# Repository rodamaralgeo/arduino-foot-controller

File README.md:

# arduino-foot-controller
Foot Controller Midi feito com um Arduino Mega

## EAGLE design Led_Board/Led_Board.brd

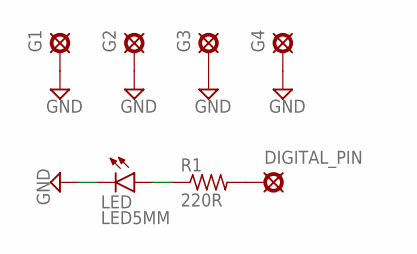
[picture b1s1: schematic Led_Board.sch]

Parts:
DIGITAL_PIN: PADO; ROUND
G1, G2, G3, G4: PADO; ROUND
LED: LED5MM
R1: 220R; R0207/3

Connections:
GND: G1.1, G2.1, G3.1, G4.1, LED.K (C)
unnamed: LED.A, R1.1
unnamed: DIGITAL_PIN.1, R1.2

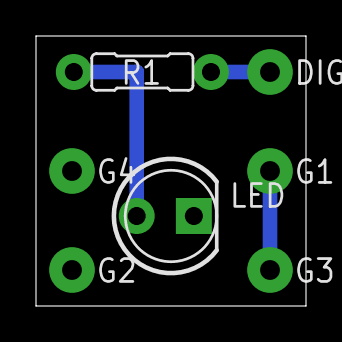
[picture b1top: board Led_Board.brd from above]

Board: 2 copper layers, 15.0 x 15.0 mm, 7 parts (0 on the bottom side), 3 nets.

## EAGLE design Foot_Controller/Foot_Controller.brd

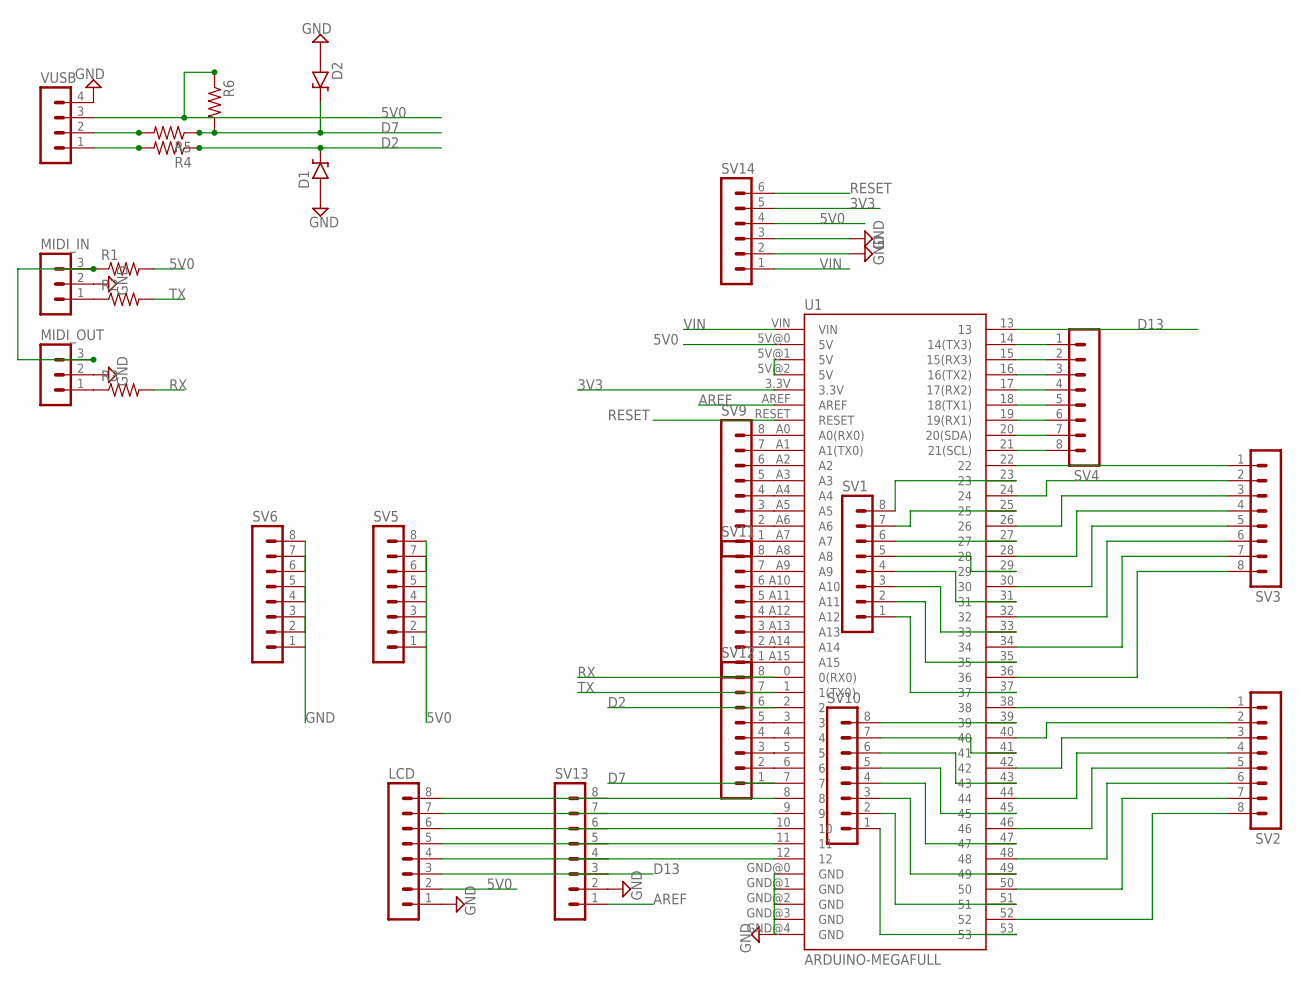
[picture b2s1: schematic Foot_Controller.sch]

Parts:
D1, D2: 1N9ZENER; DO35-3
LCD: MA08-1
MIDI_IN: MA03-1
MIDI_OUT: MA03-1
R1, R2, R3, R4, R5, R6: 6MM.3; R0207/3
SV1, SV2, SV3, SV4, SV5, SV6, SV9, SV10, SV11, SV12, SV13: MA08-1
SV14: MA06-1
U1: ARDUINO-MEGAFULL; ARDUINO_MEGA
VUSB: MA04-1

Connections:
3V3: SV14.5, U1.3.3V
5V0: LCD.2, R1.2, R6.1, SV5.1, SV5.2, SV5.3, SV5.4, SV5.5, SV5.6, SV5.7, SV5.8, SV14.4, U1.5V@0 (5V), VUSB.3
AREF: SV13.1, U1.AREF
D2: D1.C, R4.1, SV12.6, U1.2
D7: D2.C, R5.1, R6.2, SV12.1, U1.7
D13: LCD.3, SV13.3, U1.13
GND: D1.A, D2.A, LCD.1, MIDI_IN.2, MIDI_OUT.2, SV6.1, SV6.2, SV6.3, SV6.4, SV6.5, SV6.6, SV6.7, SV6.8, SV13.2, SV14.2, SV14.3, U1.GND@0 (GND), U1.GND@1 (GND), U1.GND@2 (GND), U1.GND@3 (GND), U1.GND@4 (GND), VUSB.4
unnamed: SV1.8, U1.23
unnamed: SV1.7, U1.25
unnamed: SV1.6, U1.27
unnamed: SV1.5, U1.29
unnamed: SV1.4, U1.31
unnamed: SV1.3, U1.33
unnamed: SV1.2, U1.35
unnamed: SV1.1, U1.37
unnamed: SV2.1, U1.38
unnamed: SV2.2, U1.40
unnamed: SV2.3, U1.42
unnamed: SV2.4, U1.44
unnamed: SV2.5, U1.46
unnamed: SV2.6, U1.48
unnamed: SV2.7, U1.50
unnamed: SV2.8, U1.52
unnamed: SV10.8, U1.39
unnamed: SV10.7, U1.41
unnamed: SV10.6, U1.43
unnamed: SV10.5, U1.45
unnamed: SV10.4, U1.47
unnamed: SV10.3, U1.49
unnamed: SV10.2, U1.51
unnamed: SV10.1, U1.53
unnamed: SV3.2, U1.24
unnamed: SV3.1, U1.22
unnamed: SV3.3, U1.26
unnamed: SV3.4, U1.28
unnamed: SV3.5, U1.30
unnamed: SV3.6, U1.32
unnamed: SV3.7, U1.34
unnamed: SV3.8, U1.36
unnamed: SV4.1, U1.14 (14(TX3))
unnamed: SV4.2, U1.15 (15(RX3))
unnamed: SV4.3, U1.16 (16(TX2))
unnamed: SV4.4, U1.17 (17(RX2))
unnamed: SV4.5, U1.18 (18(TX1))
unnamed: SV4.6, U1.19 (19(RX1))
unnamed: SV4.7, U1.20 (20(SDA))
unnamed: SV4.8, U1.21 (21(SCL))
unnamed: SV9.1, U1.A7
unnamed: SV9.2, U1.A6
unnamed: SV9.3, U1.A5
unnamed: SV9.4, U1.A4
unnamed: SV9.5, U1.A3
unnamed: SV9.6, U1.A2
unnamed: SV9.7, U1.A1 (A1(TX0))
unnamed: SV9.8, U1.A0 (A0(RX0))
unnamed: SV11.1, U1.A15
unnamed: SV11.2, U1.A14
unnamed: SV11.3, U1.A13
unnamed: SV11.4, U1.A12
unnamed: SV11.5, U1.A11
unnamed: SV11.6, U1.A10
unnamed: SV11.7, U1.A9
unnamed: SV11.8, U1.A8
unnamed: U1.5V@1 (5V), U1.5V@2 (5V)
unnamed: SV12.2, U1.6
unnamed: SV12.3, U1.5
unnamed: SV12.4, U1.4
unnamed: SV12.5, U1.3
unnamed: LCD.8, SV13.8, U1.8
unnamed: LCD.7, SV13.7, U1.9
unnamed: LCD.6, SV13.6, U1.10
unnamed: LCD.5, SV13.5, U1.11
unnamed: LCD.4, SV13.4, U1.12
unnamed: MIDI_OUT.1, R3.1
unnamed: MIDI_IN.1, R2.1
unnamed: MIDI_IN.3, MIDI_OUT.3, R1.1
unnamed: R4.2, VUSB.1
unnamed: R5.2, VUSB.2
RESET: SV14.6, U1.RESET
RX: R3.2, SV12.8, U1.0 (0(RX0))
TX: R2.2, SV12.7, U1.1 (1(TX0))
VIN: SV14.1, U1.VIN

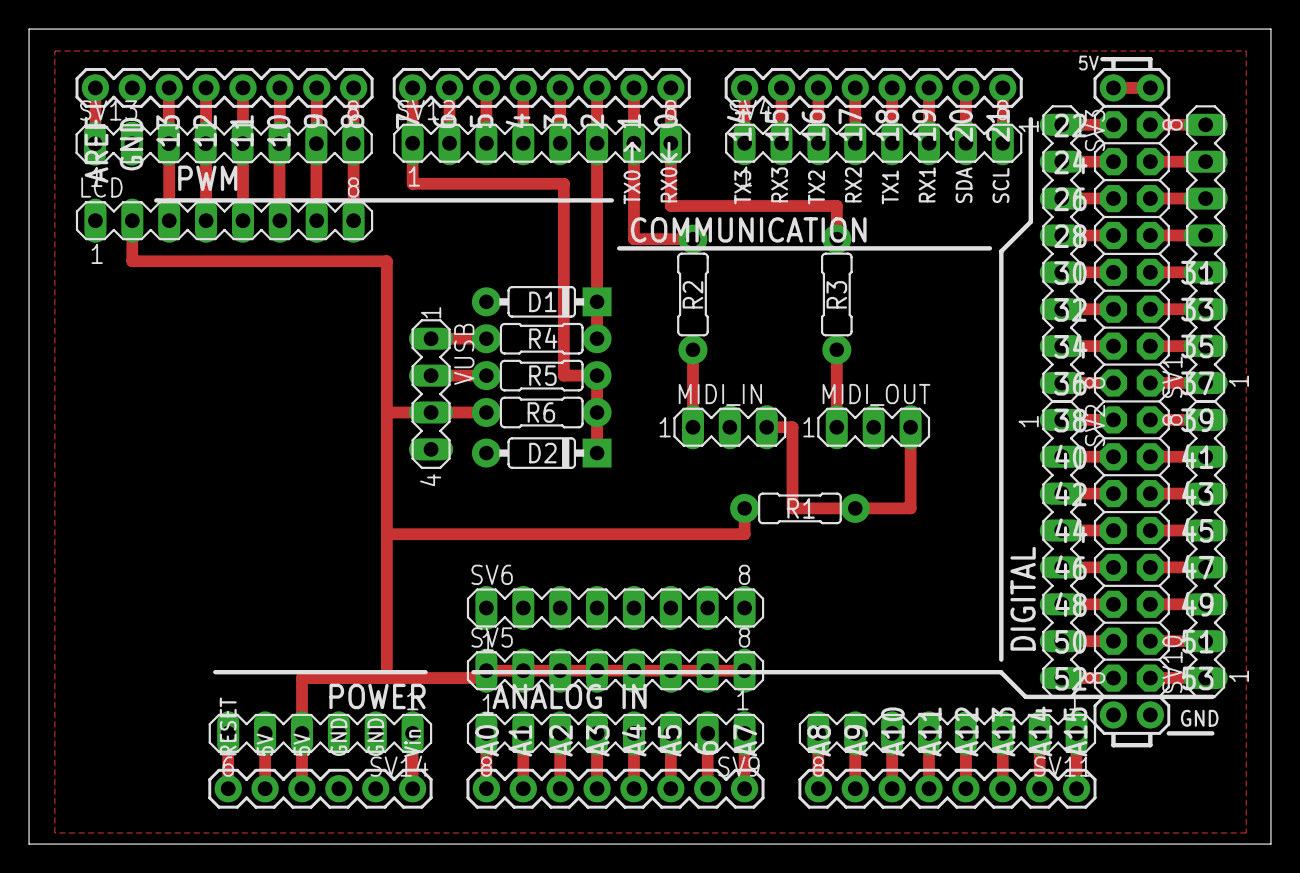
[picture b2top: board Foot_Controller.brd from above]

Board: 2 copper layers, 85.5 x 56.1 mm, 25 parts (0 on the bottom side), 82 nets.

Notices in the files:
parts and their libraries:
SparkFun-Boards: Licensing: Creative Commons ShareAlike 4.0 International - https://creativecommons.org/licenses/by-sa/4.0
